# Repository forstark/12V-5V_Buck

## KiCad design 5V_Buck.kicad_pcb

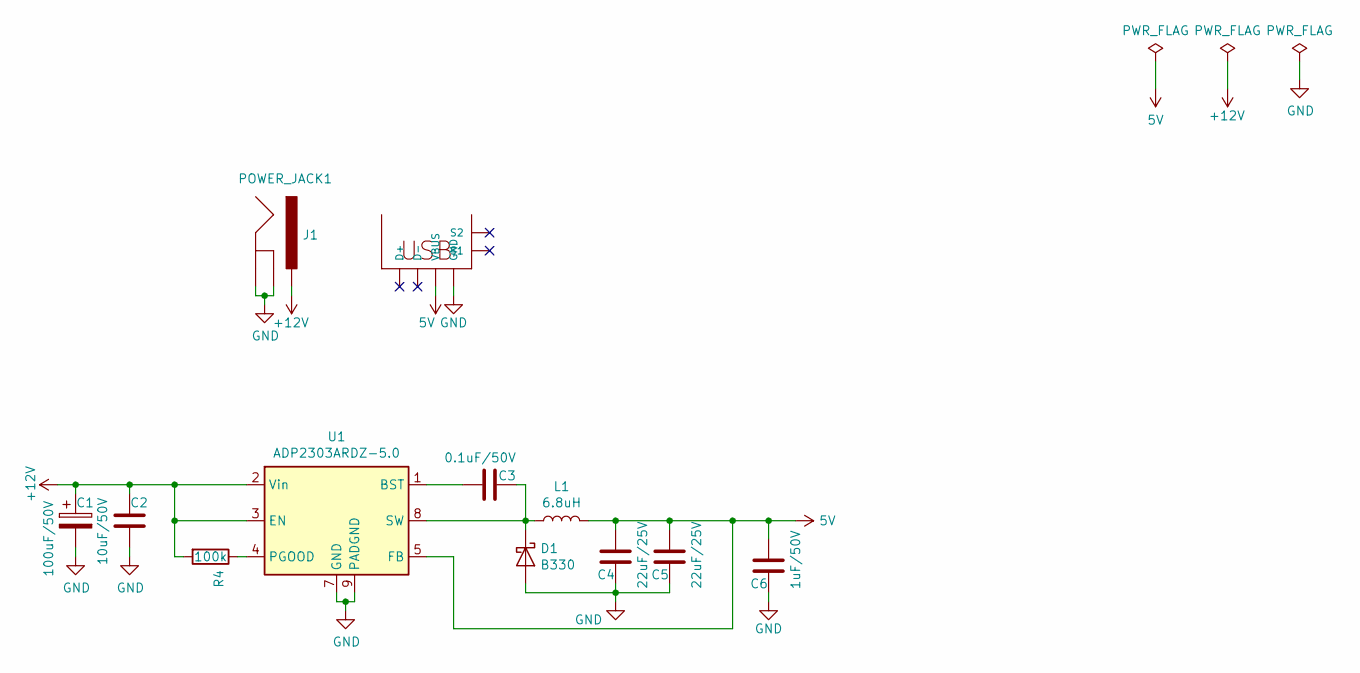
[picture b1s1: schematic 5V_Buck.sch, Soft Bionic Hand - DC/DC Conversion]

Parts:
C1: 100uF/50V; CP_Elec_8x10.5
C2: 10uF/50V; C_1206_3216Metric_Pad1.42x1.75mm_HandSolder
C3: 0.1uF/50V; C_1206_3216Metric_Pad1.42x1.75mm_HandSolder
C4, C5: 22uF/25V; C_1206_3216Metric_Pad1.42x1.75mm_HandSolder
C6: 1uF/50V; C_1206_3216Metric_Pad1.42x1.75mm_HandSolder
D1: B330; D_SMC
J1: POWER_JACK1; POWER_JACK_SMD_OVERPASTE_REDBOARD_0603
L1: 6.8uH; L_Vishay_IHLP-2020
M1: USB+SHIELDUSB-A-S-NOSILK-FEMALE; USB-A-S-NOSILK-FEMALE
R4: 100k; R_1206_3216Metric_Pad1.42x1.75mm_HandSolder
U1: ADP2303ARDZ-5.0; SOIC-8-1EP_3.9x4.9mm_P1.27mm_EP2.29x3mm

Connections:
5V: C4.2, C5.2, C6.2, L1.2, M1.VBUS, U1.5 (FB)
+12V: C1.1, C2.1, J1.VIN0 (PWR), R4.2, U1.2 (Vin), U1.3 (EN)
GND: C1.2, C2.2, C4.1, C5.1, C6.1, D1.2 (A), J1.GND (GNDBREAK), J1.P$4 (GND), M1.GND, U1.7 (GND), U1.9 (PADGND)
unnamed: C3.1, U1.1 (BST)
unnamed: C3.2, D1.1 (K), L1.1, U1.8 (SW)
unnamed: R4.1, U1.4 (PGOOD)

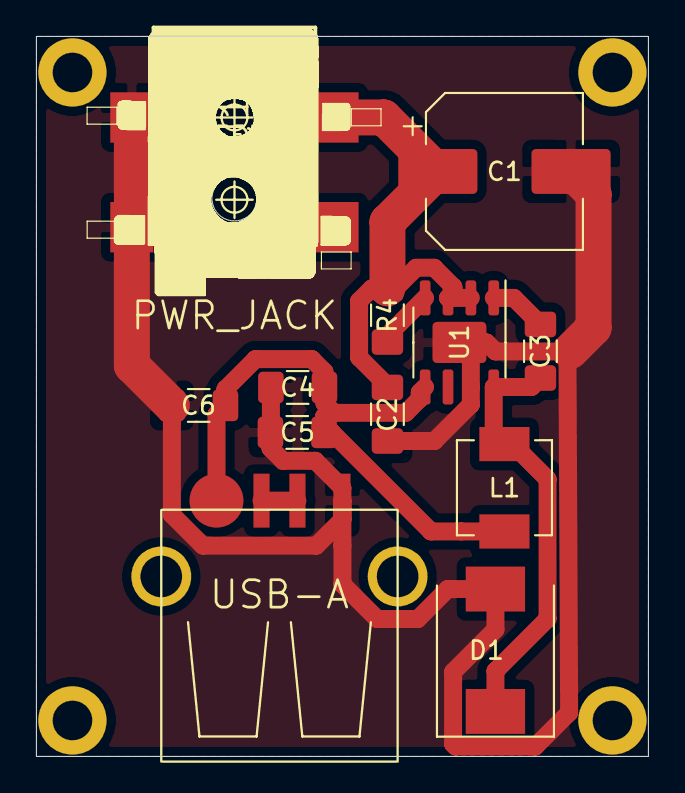
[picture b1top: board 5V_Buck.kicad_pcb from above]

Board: 2 copper layers, 34.0 x 40.0 mm, 12 parts (0 on the bottom side), 6 nets.

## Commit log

2021-04-02 Updating PCB fabrication files
2021-04-02 Updating 3D view
2021-04-02 Creating a 3D box
2021-04-02 Updating assembly
2021-04-02 Adding textures in assembly
2021-04-02 Correction of spacer size
2021-04-02 Removing temporary files
2021-04-04 Updating CNC files
2021-04-04 Adding screws to assembly
2021-04-05 Updating textures
